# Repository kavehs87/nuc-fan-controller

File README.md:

# NUC fan control — one project, two halves

This repo is what `nuc-fan-controller` and the perfboard fan‑switch build became when they were merged in
October 2026. The fan‑switch history came across with it — 22 commits and the `checkpoint-fan-driver-v1`
and `checkpoint-pro-mini-v2` tags — parked under one directory, so nothing collided.

| half | what it holds | state |
|---|---|---|
| **`fan-switch-booster/`** | the gate booster that lets a 3.3 V logic pin switch a 12 V fan: its schematic, an ngspice model with hand‑written FET models, five sketches, the bench scripts | **built on perfboard, scoped, and listened to.** It is the electrical reference |
| **root** | the record of the NUC's own fan control: 4 577 paired 1 Hz samples in `bench/data/`, the analysers and graphs that read them, `BUILD.md`, and the sketches that carry the measured ITE constants | **measured.** The enclosure board that was designed around those numbers is retired to git at the tag `nuc-fan-controller-full-2026-10-23` |

**The perfboard is the reference.** Every claim about how a 12 V two‑pin fan behaves under a chopped
supply — carrier frequency, delivered duty, the fan's start threshold, what the noise actually was — comes
from that board and is recorded in `fan-switch-booster/README.md`. Every claim about how the NUC's ITE
behaves — its PWM frequency and amplitude, where its demand bottoms out, what it follows — comes from the
breadboard runs recorded below and in `BUILD.md`. The two were measured on the same machine, and they
complement each other; they do not agree on everything, and where they differ is written down rather than
smoothed over.

In October 2026 the repo was reduced to that: one KiCad project, the one that was simulated and
perfboard‑tested. The enclosure board's drawings, its exports, its board generator, the archived
tach‑simulator board and the two abandoned routings were removed, along with every KiCad cache and scratch
copy. They are complete at the tag named above, and no measurement went with them — the ITE runs were done
on a breadboard with an Uno.

## The tree

```
README.md                  this file — the merged record, and the measured facts both halves rest on
AGENTS.md                  what is settled, so it is not re-litigated
BUILD.md                   the NUC-side bench procedures: meter the header, the divider, the BC547 check,
                           the log pairs and offsets, calibration order  (its board sections are a
                           retired record; the commands in them no longer run)

bench/                     the ITE measurements
  data/                      12 raw 1 Hz logs — every number in this file comes from these
  analyze-*.py               the five analysers
  plot-curve.py plot-hold.py draw the two graphs in docs/bench/
  prepare-photos.py          the tool that cropped docs/bench/ from the phone originals; its input
                             directory was purged, so it no longer runs

docs/
  bench/                     five bench photographs, two graphs, and a README.md naming each one
  parts-collection.*         the parts sheet: §1 the perfboard build as it actually is, §2–3 the retired
                             board's cabinet walk, §4 the measurements that decide footprints

firmware/                  the sketches that made those measurements
  nuc-tach-modeB/            the ITE constants live here
  nuc-tach-modeA/            the archived tach simulator's sketch
  probe-*/                   the five breadboard probes

fan-switch-booster/        the built reference — its own README.md and AGENTS.md
  mosfet-fan-switch.kicad_sch   the schematic the perfboard was built from
  sim/                       ngspice model, hand-written FET models, ./sim/run.sh
  firmware/                  the sketch on the chip, three earlier variants, an Arduino-as-ISP programmer,
                             and the bench scripts (set.sh, seq.sh, flash-bootloader.sh, verify-flash.sh)
  pcb/  docs/pcb-*           the retired PCB record
  archive/                   the 5 V low-side first attempt
```

Three tags mark the states this repo has been through: `checkpoint-fan-driver-v1` and
`checkpoint-pro-mini-v2` from the fan‑switch work, and `nuc-fan-controller-full-2026-10-23`, which holds
everything the October 2026 cleanup removed.

## The facts both halves rest on

| fact | value | evidence |
|---|---|---|
| the machine | 6th‑generation i3 NUC, whose stock blower is a **5 V** fan | measured |
| the ITE's PWM request | **23 kHz** square, inside Intel's 25 kHz ±10 % | measured, scope |
| top of that swing | **≈ 4.90 V** on the wire, ≈ 2.45 V at a 10 k / 10 k tap | measured, extrapolated from the dwell ladder |
| the header's own fan supply | **5 V**, and a deliberate no‑connect on both boards | measured |
| the ITE's duty **floor** | **46–48 %** — 1 946 samples, none below 100 counts of 717. Under ITE control the fan never stops | measured |
| the duty is stepped | dwell rungs 198 / 257 / 320 / 380 counts, an 11.9‑point quantum | measured |
| what the demand follows | the **board / PCH temperature**, not the cores | measured, 4 577 paired samples |
| what a tach claim does to the demand | **1.1 %** for a 5.6× claim — reported speed is not in the loop | measured |
| tach read gain | 1 186 RPM against a 1 200 RPM claim, factor **0.990** | measured |
| tach ↔ RPM | `RPM = 30 × f_tach` (ITE IT8607E counts 2 pulses per turn) | measured |
| a 12 V two‑wire fan's start threshold | **4–7 V at its terminals**; 10 % and 20 % at 100 Hz deliver 1.2 V and 2.4 V and will not start it | measured on the perfboard |
| ATmega328P absolute maximum, any pin | **VCC + 0.5 V** = 3.8 V on a 3.3 V part | datasheet |
| Intel's published pinout for these headers | **there is none** — meter the four wires before splicing | `BUILD.md` |

The floor and the start threshold fit together, which is worth saying out loud: the ITE never asks for
less than ~47 %, and 47 % at 100 Hz is about 6.4 V at the fan terminals — above the voltage the fan needs
to start. So a fan driven by the ITE's demand is never asked to start from a dead stop, and the "start
kick" left open in `fan-switch-booster/README.md` only matters for manual control below about 30 %.

## Four ways the two designs disagree, and how to not mix them

The second column is retired hardware, but its sketch `firmware/nuc-tach-modeB` is still in this repo and
still carries the measured ITE constants — so these differences are live whenever a sketch crosses over.

| | the perfboard, `fan-switch-booster/` | the retired enclosure board |
|---|---|---|
| fan drive pin | **D9** (`OC1A`), Timer 1 | **D11** (`OC2A`), Timer 2 |
| tach pin | **D10**, and unused on the bench — that board has no tach path | **D9** (`OC1A`), sinking `Q1`'s open collector |
| polarity | non‑inverting: pin high → fan on | `Q2` inverts once — pin high → gate low → fan off — and `nuc-tach-modeB` asks for the complement to undo it |
| carrier | **100 Hz**, measured quiet | **31.25 kHz**, exactly 8 MHz / 256 |
| gate stage | `Q2` 2N7002 + `Q3` IRF7416 booster. Turn‑off costs a fixed **~170 µs**, because `/BOOT` charges back through `R3` 10 kΩ into a node that measures **~8 nF** | `Q2` BC547 with **`R8` 1 kΩ pulling the gate node to +12 V**, `R9` 120 Ω in series with `Q3`'s gate, `R10` 10 kΩ across gate‑to‑source. Turn‑off dumps through 120 Ω: τ ≈ 0.2 µs |
| ADC scale at the divider tap | **775 counts** — a 3.3 V reference | the logs are on an **Uno's 5 V** reference, where the same 2.50 V is **512 counts** |

**Both carriers are correct, for their own gate stage.** 31.25 kHz is safe on the BC547 board because its
gate dumps through 120 Ω in well under a microsecond; it is *unusable* on the perfboard, where the off
half‑period (16 µs) is far shorter than the 170 µs the booster needs to turn off, so the output is simply
stuck on. That is not a contradiction, it is two different circuits. Neither has to copy the other's carrier:
the ITE's 23 kHz is only *read* — the divider turns it into a DC level — and the fan drive frequency is a
free choice. Do not feed the ITE's clock into either output stage.

**And one thing that CAD never caught up with.** The bench settled on a **10 kΩ / 10 kΩ** divider — 2.50 V on
the tap, 0.8 V of headroom on a 3.3 V part — while the retired schematic still carried `R3` 4.7 k → `R4`
2.2 k in series from `NUC_PWM`, over `R5` 10 kΩ to ground: a **2.96 V** tap with 0.34 V of headroom. If that
board is ever rebuilt from the tag, it starts at two 10 kΩ, not at what the drawing says.

## Where the fan‑switch half lives

| in `fan-switch-booster/` | what it is |
|---|---|
| `README.md` | the whole record of that half: the stages, every part from the cabinets, the simulation, the perfboard findings, why the carrier is 100 Hz, the firmware and the flashing route |
| `AGENTS.md` | the settled list for that half — read it before touching that subtree |
| `mosfet-fan-switch.kicad_sch` | the schematic the perfboard was built from. **Live** |
| `mosfet-fan-switch.kicad_pcb`, `pcb/`, `docs/pcb-*` | **retired** board design — never built, never routed. Kept as the reason the layout looks like it does |
| `sim/` | the ngspice model. `./sim/run.sh` regenerates netlist, deck, plots and the variant tables |
| `firmware/fan-switch-freq/` | the sketch on the chip right now: boots itself at `duty 0 % OCR1A 0/10000 carrier 100 Hz` |
| `firmware/bench/` | `set.sh`, `seq.sh`, `flash-bootloader.sh`, `verify-flash.sh`, and how to run them on the remote bench |
| `archive/` | the 5 V low‑side first attempt — its schematic, its placeholder models and its plots |

---

# What the NUC does on its own — measured

Everything below this line is the record of the **ITE side**: how the NUC asks for fan speed, what its
demand follows, where it bottoms out, and how it reads a tach signal. It was measured on a breadboard with an
Uno standing in for the Pro Mini, and none of it depends on any board in this repo.

## The enclosure board that used to be here

`nuc-fan-controller` was a board meant to sit inside the NUC enclosure — last drawn as 88.90 × 76.20 mm on a
single copper layer, small enough to etch at home, after an earlier life as 124 × 85 mm on two. It did four
things: brought 19 V down to 12 V with an XL4016E1 module for three 12 V two‑pin fans; made 3.3 V for a Pro
Mini with an AMS1117‑3.3, with no 5 V rail anywhere on it; read the ITE's PWM request on A0 and re‑made it at
31.25 kHz on D11 through a BC547 stage into an IRFZ44N; and answered the tach with a Timer 1 square wave on
D9 sinking `Q1`'s open collector, the pull‑up living in the NUC. ERC clean, DRC clean, 0 unconnected items,
one deliberate no‑connect on its fan‑header connector's supply pin — the header's own fan supply, which it
never touched.

**It is retired, and it was never built.** The perfboard in `fan-switch-booster/` is the reference, so that
board's KiCad project, its `exports/` (schematic, board, the 1:1 copper etch prints, BOM, Gerbers), its board
generator in `logs/`, the archived tach‑simulator board and the two abandoned routings of the booster were
removed from the working tree in October 2026. All of it is intact in git at the tag
**`nuc-fan-controller-full-2026-10-23`** — every drawing, every export, and `10bc262`, the version that built
its 19 V → 12 V converter out of discrete parts instead of the module.

What stayed is measurement rather than board: `bench/data/` and the analysers that read it, the photographs
and graphs in `docs/bench/`, `BUILD.md`, `docs/parts-collection.md`, and the sketches that produced the
numbers.

## What is here for the NUC side

| File | What it is |
|---|---|
| `fan-switch-booster/` | **the built reference** — the perfboard booster, its schematic, its simulation, its sketches, its bench scripts. Table near the top of this file |
| `firmware/nuc-tach-modeB/nuc-tach-modeB.ino` | the sketch written for the retired board, and where the measured ITE constants live: `ITE_READ_GAIN`, the demand follower, the duty clamp |
| `firmware/probe-uno/probe-uno.ino` | breadboard probe sketch for an Uno (5 V / 16 MHz): tach wave on D9 with the measured `ITE_READ_GAIN` applied, 31.25 kHz fan drive on D11 — for scope-checking the BC547 stages before the board exists |
| `firmware/probe-gain/probe-gain.ino` | sweep sketch: an exact ladder of tach claims (900–3000 RPM, 20 s each) with the fan following the ITE's demand, printing the divider's own count — measures the ITE's read gain and logs its fan curve |
| `firmware/probe-loop/probe-loop.ino` | test sketch: fan drive pinned, tach claims stepped 800 / 2000 / 4500 RPM — measures whether the ITE's demand answers the tach at all |
| `firmware/probe-temp/probe-temp.ino` | test sketch: claim frozen at 1500 RPM — measures whether the demand answers temperature, and what the ITE's floor demand is when the machine is cold |
| `firmware/probe-divider/probe-divider.ino` | test sketch: measures the divider's own ratio with nothing but the Uno, by feeding the chain from the Uno's 5 V pin so the rail voltage cancels |
| `bench/analyze-ladder.py`, `bench/analyze-temp.py`, `bench/analyze-cold.py`, `bench/analyze-heat.py` | the analysers that produced the numbers below, run against `bench/data/` — `analyze-heat.py` is the one that separates the cores from the board |
| `bench/analyze-hold.py` | the analyser for the "does it integrate time?" test: flat-window trend, same-temperature early against late, and a two-variable fit |
| `bench/plot-curve.py`, `bench/plot-hold.py` | draw `docs/bench/06-ite-fan-response.svg` and `docs/bench/07-ite-hold-test.svg`, the two graphs below, from the same logs |
| `docs/bench/` | the five bench photographs and those two graphs, with `docs/bench/README.md` naming what each one shows |
| `bench/data/` | the raw logs: 1 Hz traces of the divider reading, and of the NUC's temperatures |
| `firmware/nuc-tach-modeA/nuc-tach-modeA.ino` | the archived tach simulator's sketch — the fixed‑RPM answer this project replaced |
| `bench/prepare-photos.py` | the tool that cropped `docs/bench/` out of the phone originals. Its input directory was purged in the cleanup, so it no longer runs; the recipe is in the file |
| `docs/parts-collection.md`, `.html` | the parts sheet, in two halves: **§1 the perfboard build as it actually is** — what is fitted, what is on the schematic but not on this bench, and what is on the shelf modelled but not fitted; §2–3 the **retired** board's cabinet walk, kept because those parts are still in the drawers and this is the record of where they came from; §4 the eight measurements that decide footprints, each one now marked *still live* or *retired board's footprint detail*. The `.html` is the same sheet with tick boxes |
| `BUILD.md` | the bench sheet: identifying the four header wires with a meter, setting a buck module to 12.0 V, the divider / top‑of‑swing procedure, the BC547 pin‑order check, calibration order. Its assembly steps name parts of the retired board |
| `fan-switch-booster/archive/` | the booster's first version — a single logic‑level IRLZ44N driven directly at 5 V, with its plots. Kept because the reason it worked is the reason 3.3 V needs a booster |

## On the bench

These measurements stand on their own. They were taken on a breadboard, with an Uno standing in for the Pro
Mini and the ITE's own behaviour logged at 1 Hz — no board in this repo was needed for any of them. Full
numbers and the raw logs are in `BUILD.md` and `bench/data/`; these are the readings that changed the design.

**The whole result in one picture** — 4 577 paired samples from five runs. Top: the ITE's requested duty
against the temperature of the *board* (`pch_thermal`), every sample as a dot, the heavy line being the
median in 3 °C bins, the dotted lines the dwell levels the ITE actually holds. The open circles are the
247 samples where the cores sat at 65 °C or hotter while the board stayed under 55 °C — they land on the
floor, not on the ramp, which is what makes the board the axis and the cores not. Bottom left: the fourth
run in time, board warmed by hand with the bench fans off and the NUC's own blower at minimum, then a
four‑core load, then left alone. Bottom right: the fifth run in time, held at 68.5–69 °C for sixteen flat
minutes — the duty sits on 378 counts for all of it. `bench/plot-curve.py` draws it from `bench/data/`.

**The harness into the NUC's fan header.** Four wires, no published pinout — `BUILD.md` identifies
them with a meter before anything is spliced. The tach and PWM wires go to the breadboard; the
header's own fan supply is left unconnected, which is the same pin the retired board marked as a deliberate
no‑connect.

**The duty‑read chain.** The ITE's PWM wire through the series resistors to the tap, the tap to A0,
the bottom resistor and the caps to ground. A0 sits at the tap — put it at the far end of the chain
and nothing divides, because the AVR draws no current.

**The ITE's PWM is 23 kHz, not an assumption.** A scope on the PWM wire reads a 23 kHz square at
45 % duty mid‑sweep — inside Intel's 25 kHz ±10 % for a 4‑wire fan. At that frequency the divider and
C10/C11 are comfortably over‑specified: τ = 4.49 ms against a 43.5 µs period leaves 7 mV of ripple at
the ADC, 0.24 % of the duty span.

**The tach is read, and it is read 1 % low.** The scope on the tach line:

and the NUC's own hardware monitor, 40.000 Hz later:

1186 against a 1200 claim, 1188 at the same setting a minute later — the ITE's display steps by
2 RPM, and the gap is 0.990. That is `ITE_READ_GAIN`. Note what is on the same screen: CPU 58 °C,
memory 44 °C, motherboard ambient 40 °C. Those are the ITE's own sensors, and they turn out to be
what its fan policy runs on.

**The demand answers the board's temperature, not the cores, and not the reported speed.** Five tests,
all logged at 1 Hz, 4 577 paired samples. Stepping the claimed RPM 800 → 2000 → 4500 — a 5.6× swing —
moved the ITE's requested duty by 1.1 %, while the same claim swung 195–260 counts on its own: the
reported speed is not in the loop. Freezing the claim at 1500 RPM and driving the package 55 → 83 → 53 °C
moved the reading 231 → 327 → 230 counts, correlated at **r = +0.822 with a 4 s lag** — but that run had
the bench fans switched by hand, so the board rose with the cores (PCH 52 → 63.5 °C) and the two could not
be told apart.

The third run tells them apart. Same sketch, same frozen claim, bench fans at maximum: `stress-ng --cpu 4`
for 300 s took the package 34 → 73 °C and it cooled back to 38 °C, the PCH only reached 55.5 °C, and
**the demand did not move at all** — 195–260 counts for eleven minutes, r = +0.049 against the cores. The
fourth run goes the other way and pushes the top end out: bench fans off, the NUC's own blower at minimum,
the board warmed by hand and then loaded, taking the board to 68.5 °C while the cores sat pinned at
88 °C. The demand climbed to **380 counts, 74 %**, with 434 counts (85 %) seen. Binned by the board, all
four runs together:

| board (`pch_thermal`) | n | median demand | as duty, 512 counts = 100 % | PWM wire average |
|---|---|---|---|---|
| 33–51 °C | 2 131 | 239 counts | 46.7 % | 2.33 V |
| 51–54 °C | 306 | 247 counts | 48.2 % | 2.41 V |
| 54–57 °C | 251 | 254 counts | 49.6 % | 2.48 V |
| 57–60 °C | 169 | 259 counts | 50.6 % | 2.53 V |
| 60–66 °C | 365 | 319 counts | 62.3 % | 3.12 V |
| 66–72 °C | 1 352 | 377 counts | 73.6 % | 3.68 V |

The decisive 247 samples have the cores at 68.7 °C and the board at 51.0 °C, and the ITE asks for exactly
what it asks for when everything is cold: 243 counts, 47 %, no sample above 261. `bench/analyze-heat.py`
reproduces these tables from the logs.

Two corrections to what this README said before the fourth run. The 297 counts it listed at 57–60 °C was
not a step the ITE holds — 285–314 counts account for 55 samples out of 4 577, while the four rungs
195–206, 253–264, 315–326 and 373–384 account for 667, 1 120, 321 and 826: the ITE dwells on rungs and
passes through everything else on its way between them.
And the demand does not chase the board at the same speed in both directions. In the fourth run the board
crossed 55 °C and the demand took **about 75 s** to reach its plateau, while on the way back it went
381 → 242 counts **within 30 s** of the board falling back through the same knee. The follower's 15 s tau
sits well inside both, so it filters the ITE's cycling without fighting its response.

**It is not an integrator: 20 minutes with the board held hot does not make the duty climb.** The theory
worth killing was that the ITE raises its duty for as long as the temperature refuses to fall — that it
integrates dwell time, and maybe accelerates past some threshold. The earlier runs could not touch it,
because in all of them the temperature was moving while the demand was being measured. The fifth run is
built for the question: a 300 s four‑core ramp to push the board past the knee, then **1200 s at a lighter
two‑core load** so the board sits still, then 300 s left alone. The board settled at 68.5–69 °C and stayed
there for sixteen flat minutes with the cores at 84–86 °C, and the demand sat at **378 counts** — the same
6/8 rung the fourth run found at the same board temperature, repeatable to 2 counts.

Three independent reads, all saying the same thing (`bench/analyze-hold.py`):

- Across the 16 windows where the board held within 0.8 °C of its plateau, the demand trended
  **+0.6 counts per minute** — and the board's own +0.07 °C/min drift already explains +1.5 counts per
  minute at the ladder's 20 counts per °C. Nothing is left over for time to explain.
- The same board temperature reached quickly against reached and held: at 63–66 °C, 342 counts on the ramp
  against **319** in the hold; at 66–69 °C, 378 against **368**. Later is *lower*, not higher.
- Fitting the 1 513 samples above the knee on board temperature **and** seconds since the knee was crossed:
  temperature alone gives R² 0.669, adding time gives 0.670 with a coefficient of **−0.00 counts per
  minute**. Time does not earn its place in the model.

What the run found instead is the opposite of a ratchet: held steady, **the ITE stops hunting**. Early in
the hold the reading swung 318–380 counts, dipping to the rung below; by the end the dips had shrunk to
346–381 and the mode was 379 throughout. And the ramp's overshoot — 342 counts at 63–66 °C on the way up
against 319 counts at the same temperature in the hold — says the ITE answers how *fast* the board is
moving as well as where it is, which is the same asymmetry the fourth run measured as 75 s to climb and
30 s to release. For the build this is a simplification: `DEMAND_TAU_S` does not have to outwait a
controller that ramps on a timer, because this one does not.

**The demand has a floor, and it is not near zero.** With the fans at maximum the package sat at 32–36 °C
for twelve minutes — 21 °C below the plateau the first temperature run had been stuck at — and the duty
did not follow it down: 196–260 counts, median 239, and not one sample of 717 below 100 counts. The floor
is 46–48 % duty, 2.33 V on the PWM wire, and it holds from the coldest measured board to a PCH of about
54 °C — 1 946 samples of it. So the fan this board drives never stops: `FAN_DUTY_MIN` is a clamp against a
broken sense wire rather than something the ITE ever reaches, and a fan that is always turning is a fan
whose tach claim is always plausible.

The fan also sits **inside** the ITE's loop — the fan cools the board, the ITE reads the board, the ITE
changes the demand — which is an enclosure requirement rather than a firmware one: air has to move across
the board and the ITE's own ambient sensor (the BIOS screen's "motherboard ambient", 40 °C against a CPU
at 58 °C), not only over the heatsink. The ITE will sit at its floor quite happily while the cores are at
73 °C.

**The demand is stepped, and the ladder holds across five runs.** The dwell levels are 198, 257, 320 and
380 counts, spaced 59–63, held for 667, 1 120, 321 and 826 samples of 4 577, and the hottest samples reach
434 — close to the fifth rung the spacing predicts, 441. A straight line through the four is counts = 15 + 61·k for k = 3, 4, 5, 6, so the step
is 11.9 duty points and 0.595 V on the wire: a binary duty quantum of 1/8, with the ITE sitting on 3/8 when
the board is cold and reaching 6/8 or 7/8 when it is hot. Read as 605 counts the step is 10.1 points and
matches nothing, which is one more reason the 10 kΩ / 10 kΩ divider is the right one. The cycling is fast —
535 of 716 seconds moved by more than 3 counts, one dwell switching to the other in 1–3 s — so the follower
filters it (tau 15 s, 1.5 duty point deadband) instead of pumping the fan at 0.3 Hz while the machine's own
thermal time constant is minutes. The cycle is the ITE closing its loop through the fan: it asks for more
duty, the board cools, it asks for less.

**The divider is settled: two 10 kΩ.** The tap is half the PWM line, so on the Uno 512 counts is 100 %
duty and every count in `bench/data/` reads on that scale. In volts, which is what a meter should agree
with: the ITE's four dwell levels — 198, 257, 320 and 380 counts — are **0.97 V, 1.26 V, 1.56 V and 1.86 V
at A0**, i.e. **1.94 V, 2.51 V, 3.13 V and 3.71 V average on the PWM wire**. That also argues for changing
the board's divider from 4.7 kΩ + 2.2 kΩ over 10 kΩ to 10 kΩ / 10 kΩ: 2.50 V on the tap instead of 2.96 V,
0.8 V of headroom on a 3.3 V part instead of 0.34 V, one fewer resistor, and bench and board reading the
same scale.

**One thing the bench still has to settle: the top of the PWM swing.** The four dwell levels now pin it
down without a scope. Extrapolated, the ladder reaches 15 counts (0.14 V) at zero duty and **502 counts
(4.90 V) at 8/8** — so the ITE's top is nearer 4.9 V than the 5.5 V the fan header's own supply would
suggest, and 100 % lands within 2 % of 512 counts rather than at 1009. Two things are still unexplained and
a meter settles both in one sitting: why the ladder has a 15‑count offset at zero (the ITE's output, or the
reading), and whether the top is flat or droops under load at the top dwell. The procedure is in `BUILD.md`.

## Bench order that carries over to any build

1. Identify the four NUC fan‑header wires with a meter — Intel publishes no pinout.
2. Set a buck module to 12.0 V with a meter before it is wired in and confirm its current limit is
   released; confirm 3.3 V at the regulator before it ever reaches a Pro Mini.
3. Find the fan's stall duty and measure its RPM at two duties. On the perfboard the stall is already
   bracketed: 20 % delivers ~2.4 V and will not start the fan, 30 % does.
4. Read the tach output with a frequency counter — it must equal `rpm / 30` Hz exactly, it is a hardware
   timer.
5. Wire the tach side first, then the PWM wire, then the fans.

**Three things that break hardware:** a 12 V fan's tach or PWM wire spliced into the NUC header
(that fan pulls those lines to its own 12 V internally), a 5 V FTDI on a 3.3 V Pro Mini
(ATmega328P absolute maximum on any pin is VCC + 0.5 V), and a BC547 fitted in the onsemi
**C‑B‑E** order when the footprint you are using is drawn for the NXP/Philips **E‑B‑C** order — meter
the two of them before they go in, `BUILD.md` says how. Flash with Board → *Arduino Pro or Pro
Mini*, Processor → **ATmega328 (3.3V, 8MHz)**.

## Reproducing the measurements

From the repo root, against the raw 1 Hz logs in `bench/data/`. Each Uno log is paired with its temperature
capture by a fixed offset in seconds — the Uno log has no timestamps — and these are the offsets the recorded
numbers were produced with:

```sh
# which temperature the ITE's demand follows: the table in *On the bench*
python3 bench/analyze-heat.py \
    bench/data/temp.log    bench/data/stress.log         -4 \
    bench/data/cold.log    bench/data/coldtemp.log        0 \
    bench/data/stress2.log bench/data/stress2-temps.log -15 \
    bench/data/warm.log    bench/data/warm-temps.log    -20 \
    bench/data/hold.log    bench/data/hold-temps.log    -20

# does the ITE integrate the time the board spends hot?
python3 bench/analyze-hold.py bench/data/hold.log bench/data/hold-temps.log -20

# the dwell rungs and the duty quantum
python3 bench/analyze-ladder.py bench/data/loop.log

# the two graphs
python3 bench/plot-curve.py
python3 bench/plot-hold.py bench/data/hold.log bench/data/hold-temps.log -20
```

Re‑run 2026‑10‑23, so this is verified rather than remembered: the five runs pair to 260 + 717 + 660 + 1 140
+ 1 800 = **4 577 samples**, `analyze-heat.py` reproduces the 2 131 / 306 / 251 / 169 / 365 / 1 352 board bins
and both discriminating subsets — 247 samples with the cores at 68.7 °C and the board at 51.0 °C at 243
counts, and 134 samples the other way round at 243 counts — and `analyze-ladder.py` reproduces the −1.1 %
answer to a 5.6× tach claim.

The plotters need matplotlib. The two shipped SVGs were drawn with **3.11.2**, which is not installed on this
machine; the venv that has matplotlib here has 3.10.3. Re‑running a plotter rewrites the tracked SVG with that
version's layout, so revert the change unless redrawing is what you wanted.

The booster's simulation, from `fan-switch-booster/`:

```sh
./sim/run.sh                                    # netlist -> ngspice -> variants -> plots
V=/Users/kaveh/Documents/Projects/schemdraw-mcp-server/.venv/bin/python3
$V sim/variants.py && $V sim/plot.py            # if the default python3 has no matplotlib
```

The board machinery that used to live in `logs/` — `build1l.py`, `layout.py`, `genwires.py`,
`applywires.py`, `verify.py`, `pourcheck.py`, `export.sh` — went with the retired board, and it was already
partly parked: `layout.py` and the wire generators still described the schematic as it was before it was
edited by hand, so running them would have undone work. All of it is at the tag.

One rule `genwires.py` enforced the hard way is worth keeping, because it is true of any KiCad sheet: **a
symbol pin or a name tag only connects to a wire *end***. A net whose wire carries a flag or a tag mid‑span
has to be written as the chain of segments it really is. Written as one straight wire, the flag and the tag
are orphaned and ERC reports them.

## Status

**Built, scoped and listened to:** the perfboard fan‑switch booster in `fan-switch-booster/`. Running at a
100 Hz carrier, quiet across the duty range, with the whole ladder heard.

**Measured and recorded:** the NUC's own fan control — its PWM frequency and amplitude, how it reads the
tach, what drives its demand, where that demand bottoms out and where it tops out, and that it does not
integrate the time the board spends hot. See *On the bench*; `BUILD.md` is the bench sequence.

**Retired:** the `nuc-fan-controller` enclosure board, and the archived boards before it. See *The enclosure
board that used to be here*.

**Open items:**

1. a sketch that reads `/DEMAND` on A0 and re‑makes it at the perfboard's own 100 Hz — the two halves
   joined, but the wire between them is not written yet;
2. the fan's exact start threshold, still only bracketed between 20 % and 30 % at 100 Hz, and the start kick
   that would make the bottom of the range usable;
3. `FAN_RPM_MIN`, `FAN_RPM_FULL` and `ADC_AT_100PCT` in `firmware/nuc-tach-modeB` are placeholders, and
   `ITE_READ_GAIN` was measured with an Uno — all four need the same measurement on a 3.3 V Pro Mini;
4. if the enclosure board is ever rebuilt, its divider starts at 10 kΩ / 10 kΩ, not the 4.7 k + 2.2 k over
   10 k the retired schematic still carries.

No license is granted — all rights reserved. It is published so the drawings and the reasoning
behind them are readable.

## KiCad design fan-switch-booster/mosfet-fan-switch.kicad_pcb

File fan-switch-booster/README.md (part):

# 12 V fan switched by 3.3 V logic — a gate booster built from my own parts

A KiCad schematic, a real ngspice simulation, and the same circuit **actually built and running on
perfboard** — of the thing every 3D printer needs: **an Arduino pin turning 12 V fans on and off
with a MOSFET.**  And since the design grew a NUC fan-header socket, the same Arduino can read the
NUC's own fan request and answer on its tachometer line.

**What is finished.** The perfboard build *is* the circuit: it runs, it is quiet across the duty
range, and it needs no replacement board. The KiCad board and `pcb/` are kept as the design record
— retired, not waiting to be routed or fabbed. The part of this project that actually changed
something is the measurement work under *Firmware, and why 0 % was humming*: why 0 % hummed, and why
the carrier is 100 Hz.

Every real component on this sheet is a part that actually sits in my parts cabinets
(`L1` and `R1`). Nothing here is a catalogue placeholder. The fan model is sized to the
fans I actually use: **100 mA each at 12 V.**

```
Arduino D9 (3.3 V PWM)
      |
     R1 1k ---- Q2  2N7002   level shifter: 3.3 V logic pulls /BOOT down to ~0 V
      |                |
     R2 10k          /BOOT ---- Q3  IRF7416 (P-ch)  gate booster: switches +12 V onto the gate
      |                |               |
     GND            R3 10k          R4 1k
                                     |
                                   /GATE ---- Q1  IRFZ44N  the switch that carries the fans
                                     |             |
                                    R5 10k       /DRAIN --- 12 V fan(s) --- +12 V
                                    GND             |
                                                 D1 1N5819 (flyback, cathode to +12 V)

NUC fan header J4
  PWM request 5 V --R7 10k--.  R8 10k to GND  -> /DEMAND 2.50 V at full request -> A0
  tach answer  <--Q4 BC547--  base via R9 1k from /TACH_PWM (D10, 100 Hz carrier)
  +12 V pin    not connected            the fans are powered by this board's own brick
```

Run everything with one command:

```bash
./sim/run.sh
```

It exports the netlist from the schematic, runs ngspice, writes five plots and two
comparison tables, and prints the numbers that matter. Output lands in `sim/out/`
(git-ignored).

---

## The stages, and the nets they live on

| net | what it is | who drives it |
|---|---|---|
| `/PWM` | the Arduino pin (D9 = OC1A, timer 1 channel A) | Arduino Pro Mini 3V3 |
| `/LGATE` | 2N7002 gate, held at 3.0 V by the R1/R2 divider | `/PWM` through R1 1k |
| `/BOOT` | booster node: +12 V when the pin is low, ~0 V when it is high | R3 10k up, Q2 down |
| `/HIGATE` | +12 V handed to the power FET by Q3 | Q3 IRF7416 |
| `/GATE` | IRFZ44N gate, settles at **10.91 V** | R4 1k from `/HIGATE`, pulled down by R5 10k |
| `/DRAIN` | the switching node under the fan(s) | Q1 IRFZ44N, clamped by D1 |
| `/FAN_W` | between a fan's winding and its drag resistance | fan model L1 + R6 |
| `/NUC_PWM` | the NUC's own fan request, 5 V at J4 pin 1 | the NUC (V3 in simulation) |
| `/DEMAND` | that request halved and smoothed for a 3.3 V ADC input | R7/R8 divider, C5 + C6 |
| `/TACH_PWM` | the Pro Mini's answer, D10 = OC1B, a 100 Hz carrier | Arduino Pro Mini 3V3 |
| `/TBASE` | `/TACH_PWM` after R9 1k, into Q4's base | R9 1k |
| `/NUC_TACH` | the tach line the NUC reads, pulled up inside the NUC | Q4 as an open collector |

**Why `/GATE` is 10.9 V and not 12 V.** A MOSFET gate draws no steady current, so R4 and
R5 are simply a divider: 12 V × 10 k / (1 k + 10 k) = 10.91 V. That is still deep inside the
region where the IRFZ44N's 17.5 mΩ is specified. R5 exists to keep the gate firmly at 0 V
when the pin is low, so the fan cannot drift on.

**Why the logic is not inverted.** Two inversions (Q2 inverts, Q3's P-channel orientation
inverts again) cancel. Pin high → fan on. At power-up the pin is floating, R2 keeps Q2 off,
so Q3 is off, so Q1 is off. The fans stay off.

**Why Q3's source must be the +12 V terminal.** A P-channel device's body diode conducts
drain → source. Wire Q3 the other way round and that diode feeds +12 V straight into
Q1's gate through R4 — the fans would be permanently on and no amount of code would fix it.
This is the single easiest way to get this circuit wrong, so the sheet draws Q3 rotated
180° with its source on the rail.

---

## The NUC fan-header link

The same board also talks to a PC. A NUC's 4-pin fan header wants to drive a fan itself:
it puts out a PWM **request**, expects a tachometer **answer** on the second pin, and
supplies the fan on the third. This board refuses both jobs and does them anyway:

```
NUC fan header J4                Pro Mini (on the board, U1)
  1  PWM request, 5 V ──R7 10k──┐
  2  tach answer   <──Q4 BC547──┼── D10 (OC1B)  /TACH_PWM  100 Hz carrier out
  3  fan supply    not connected│   (5 V on a 6th-gen NUC, 12 V on newer ones)
  4  GND ───────────────────────┴── GND (shared with the 12 V brick)
                                 A0  /DEMAND   2.50 V at full request, read as 775 counts
                                 D9  /PWM      the fan drive, unchanged
        R8 10k from /DEMAND to GND, with C5 1µ + C6 100n across it
```

- **The request has to be knocked from 5 V to 3.3 V** before it touches an Arduino pin.
  R7 (10 k, in series at the header) and R8 (10 k, to ground) halve it; C5 + C6 turn the
  23 kHz square wave into a DC level (τ = 5.49 ms, ≤ 5 mV ripple). Full request =
  **2.50 V = 775 counts**, 0.80 V of headroom. The NUC's PWM output only has to source
  **250 µA**.
- **The answer is an open collector**, because the pull-up lives in the NUC: R9 (1 k) into
  a BC547's base, collector on the tach line. 2.58 mA of base drive sinks 4.96 mA of
  pull-up current; the line lands at **0.037 V** low, 5.00 V high.
- **The tach carrier is a separate signal.** An ITE counts two pulses per revolution, so
  `RPM = 30 × f_tach`, and the legal window (700–10 500 RPM) is **23–350 Hz** on that
  wire. Copying the 1 kHz fan drive onto it would read 30 000 RPM and be rejected, so D10
  generates its own 100 Hz carrier (which reads 3 000 RPM). "Same PWM being sent to the
  fans" is the right *idea* — the frequency is what has to differ.
- J4 pin 3 (the NUC's own fan supply) is **not connected**: the fans are powered by this
  board's 12 V brick. Note that this supply is **not 12 V on every NUC** — a 6th-generation NUC
  drives its stock blower at **5 V**, and the ITE's PWM wire tops out near **4.9 V**, not the
  5.5 V a header supply would suggest. Nothing here depends on that pin, which is the point of
  leaving it unconnected.

### Measured on a real NUC — the record is at the root, not here

The ITE side of this design was assumed here and **measured** one directory up: 4 577 paired samples at
1 Hz on a 6th‑generation i3 NUC, logged in `../bench/data/`, analysed by `../bench/analyze-*.py`, and
tabulated with their evidence in **`../README.md`**, *The facts both halves rest on*. Read them there — they
are deliberately not repeated here. Those numbers govern, not the assumptions below.

Three of them decide how this board is used:

- the ITE's duty has a **46–48 % floor**, so under ITE control the fan never stops, and "the NUC controls
  the speed" means a ladder of roughly **47 % → 85 %**, not a knob. An actually stopped fan has to be a
  threshold in the sketch;
- a 5.6× tach claim moved the demand **1.1 %** — the tach answer exists to keep the BIOS happy, not to
  close a loop;
- the counts in `../bench/data/` are on an **Uno's 5 V** ADC reference, where 512 counts is full duty. On
  this board's **3.3 V / 8 MHz Pro Mini** the same 2.50 V tap is **775 counts**. Carry the calibration as
  volts, or multiply counts by 5 / 3.3.

The enclosure board those measurements were designed for — `nuc-fan-controller`, with its 19 V → 12 V
module, its BC547 gate stage and its 31.25 kHz drive on D11 — is **retired**: the perfboard here is the
reference. That design is intact in git at the tag `nuc-fan-controller-full-2026-10-23`, and the sketch
that carries the measured ITE constants, `../firmware/nuc-tach-modeB/nuc-tach-modeB.ino`, is still here.

`sim/nuc_link.py` (run by `./sim/run.sh`) is the check: duty-by-duty tap voltage, ripple,
ADC counts, the divider's load, the tach levels and the carrier window. Numbers and
caveats: `docs/pcb-notes.md`, *The NUC link*.

---

## Parts — all from my cabinets

| ref | part | package | cabinet · drawer | qty in bin |
|---|---|---|---|---|
| U1 | Arduino Pro Mini (3.3 V / 8 MHz, ATmega328P) | 35-hole module, on female sockets | L1 · C5 | 1 |
| Q1 | IRFZ44N N-channel power MOSFET | TO-220 | R1 · B4 | 12 |
| Q2 | 2N7002 N-channel MOSFET | SOT-23 | R1 · A4 | 11 |
| Q3 | IRF7416 P-channel MOSFET | SO-8 | R1 · A4 | 6 (+1 already on a breakout board) |
| Q4 | BC547 NPN small-signal transistor | TO-92 | R1 · D3 | 20 |
| D1 | 1N5819 Schottky, 40 V / 1 A | DO-41 | L1 · E1 | 30 |
| D2 | 1N5822 Schottky, 40 V / 3 A — **spare footprint, not soldered** | DO-27 | L1 · E1 | 9 |
| D3 | MBR10100CT Schottky, 100 V / 10 A dual — **spare footprint, not soldered** | TO-220 | L1 · E1 | 3 |
| R1, R4, R9 | 1 kΩ through-hole | axial | R1 · A2 | 20 |
| R2, R3, R5, R7, R8 | 10 kΩ through-hole | axial | R1 · B2 | 20 |
| C3, C6 | 100 n (104) ceramic disc | radial | L1 · C9 | 30 |
| C4 | 10 µ 16 V electrolytic | radial, 6.3 mm | L1 · C1 | 20 |
| C5 | 1 µ 50 V electrolytic | radial, 8 mm | L1 · E7 | 8 |
| V1 | Switching Power Supply Module, 12 V 450 mA | module | L1 · B7 | 2 |

These items on the sheet are **not** bin parts. They carry `dnp yes` (do not populate)
and have no footprint on the board:

- **C1 = 1.5 nF** — the IRFZ44N's own input capacitance (Ciss ≈ 1489 pF), drawn explicitly.
- **C2 = 1.7 nF** — the IRF7416's Ciss (≈ 1700 pF), drawn explicitly.
- **L1 = 10 mH + R6 = 120 Ω** — the fan. My bins hold no 12 V fan, so the fan is a model: an
  inductor for the winding and a resistor for the mechanical load. 12 V / 120 Ω = **100 mA**,
  which is what my real fans draw. Change R6 if yours are different: 80 Ω models a 150 mA fan.
- **V2, V3, V5** (VPULSE sources) stand in for the three pins: D9's fan drive, the NUC's
  5 V / 23 kHz request at J4 pin 1, and D10's 100 Hz tach carrier. **V4 + R10** stand in for
  the 5 V and 1 kΩ pull-up the NUC carries on its own tach line.
- The KiCad symbol for U1 is `mosfet-fan-switch:Arduino_Pro_Mini_328`, generated by
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
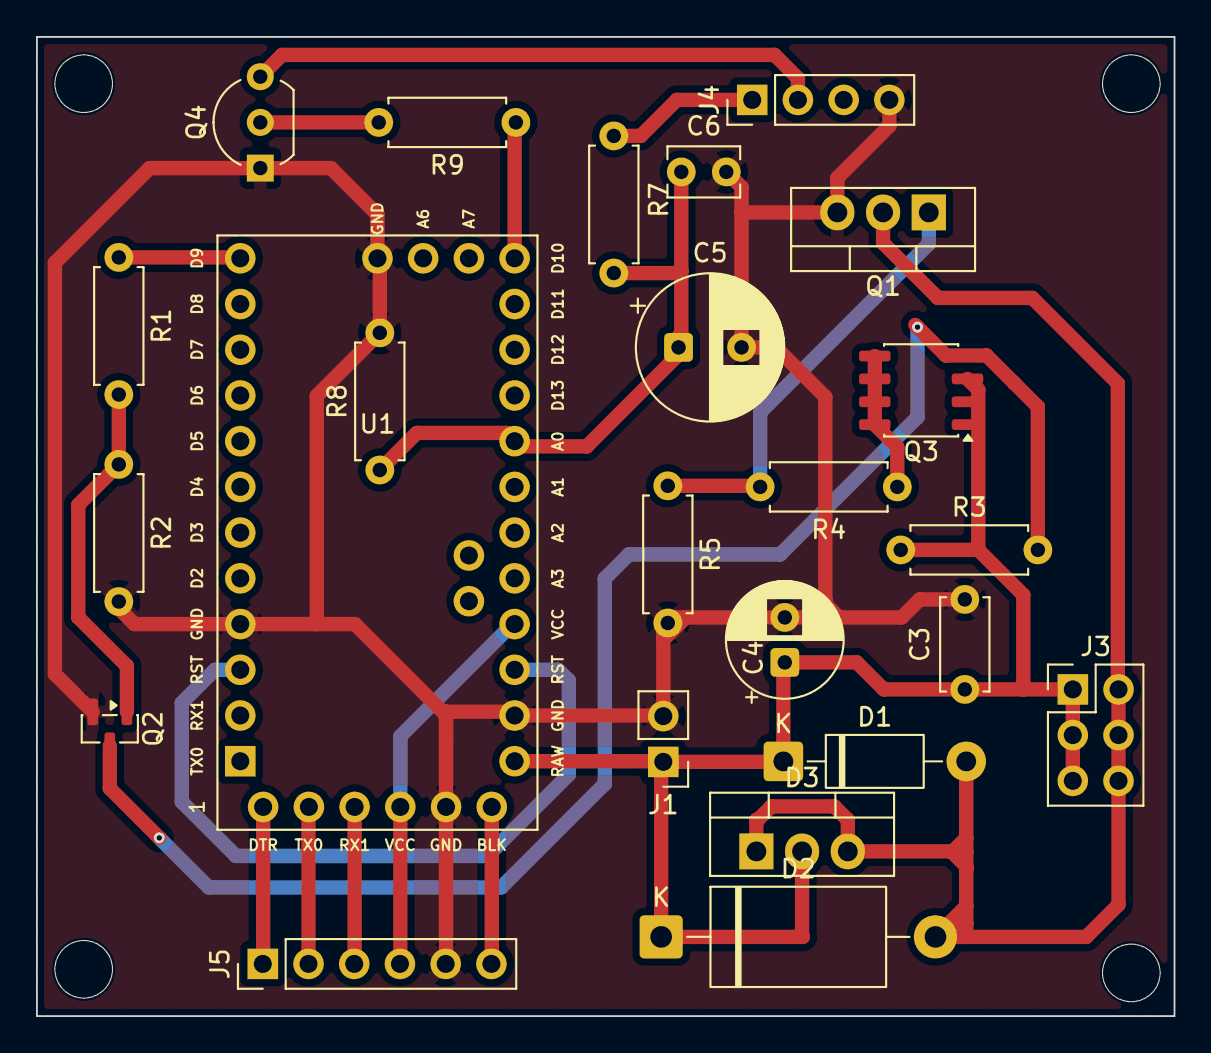
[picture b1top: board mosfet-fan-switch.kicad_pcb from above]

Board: 2 copper layers, 63.2 x 54.4 mm, 28 parts (0 on the bottom side), 19 nets.

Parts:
C3: 100n; C_Disc_D5.0mm_W2.5mm_P5.00mm
C4: 10u; CP_Radial_D6.3mm_P2.50mm
C5: 1u; CP_Radial_D8.0mm_P3.50mm
C6: 100n; C_Disc_D3.8mm_W2.6mm_P2.50mm
D1: 1n5819; D_DO-41_SOD81_P10.16mm_Horizontal
D2: 1n5822; D_DO-27_P15.24mm_Horizontal
D3: mbr10100ct; TO-220-3_Vertical
J1: 12V IN; PinHeader_1x02_P2.54mm_Vertical
J3: FAN OUT; PinHeader_2x03_P2.54mm_Vertical
J4: NUC FAN HEADER; PinHeader_1x04_P2.54mm_Vertical
J5: FTDI HEADER; PinHeader_1x06_P2.54mm_Vertical
MK1, MK2, MK3, MK4: M3 mounting hole; MountingHole_3.2mm_M3
Q1: irfz44n; TO-220-3_Vertical
Q2: 2n7002; SOT-23
Q3: irf7416; SO-8_3.9x4.9mm_P1.27mm
Q4: BC547; TO-92_Inline_Wide
R1, R4, R9: 1k; R_Axial_DIN0207_L6.3mm_D2.5mm_P7.62mm_Horizontal
R2, R3, R5, R7, R8: 10k; R_Axial_DIN0207_L6.3mm_D2.5mm_P7.62mm_Horizontal
U1: Arduino_Pro_Mini_3V3; Arduino_Pro_Mini_328_Socket

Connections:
/BLK: J5.6, U1.30 (BLK)
/BOOT: Q2.3 (D), Q3.4 (G), R3.2
/DEMAND: C5.1, C6.1, R7.2, R8.1, U1.20 (A0)
/DRAIN: D1.2 (A), D2.2 (A), D3.1 (A), D3.3 (A), J3.2, J3.4, J3.6, Q1.2 (D)
/DTR: J5.1, U1.25 (DTR)
/GATE: Q1.1 (G), R4.2, R5.1
/GND: C3.2, C4.2, C5.2, C6.2, J1.2, J4.4, J5.5, Q1.3 (S), Q2.2 (S), Q4.1 (E), R2.2, R5.2, R8.2, U1.4 (GND), U1.14 (GND), U1.29 (GND), U1.31 (GND)
/HIGATE: Q3.5 (D), Q3.6 (D), Q3.7 (D), Q3.8 (D), R4.1
/LGATE: Q2.1 (G), R1.2, R2.1
/NUC_PWM: J4.1, R7.1
/NUC_TACH: J4.2, Q4.3 (C)
/P3V3: J5.4, U1.16 (VCC), U1.28 (VCC)
/P12V: C3.1, C4.1, D1.1 (K), D2.1 (K), D3.2 (K), J1.1, J3.1, J3.3, J3.5, Q3.1 (S), Q3.2 (S), Q3.3 (S), R3.1, U1.13 (RAW)
/PWM: R1.1, U1.12 (D9)
/RST: U1.3 (RST), U1.15 (RST)
/RX1: J5.3, U1.27 (RX1)
/TACH_PWM: R9.1, U1.24 (D10)
/TBASE: Q4.2 (B), R9.2
/TX0: J5.2, U1.26 (TX0)

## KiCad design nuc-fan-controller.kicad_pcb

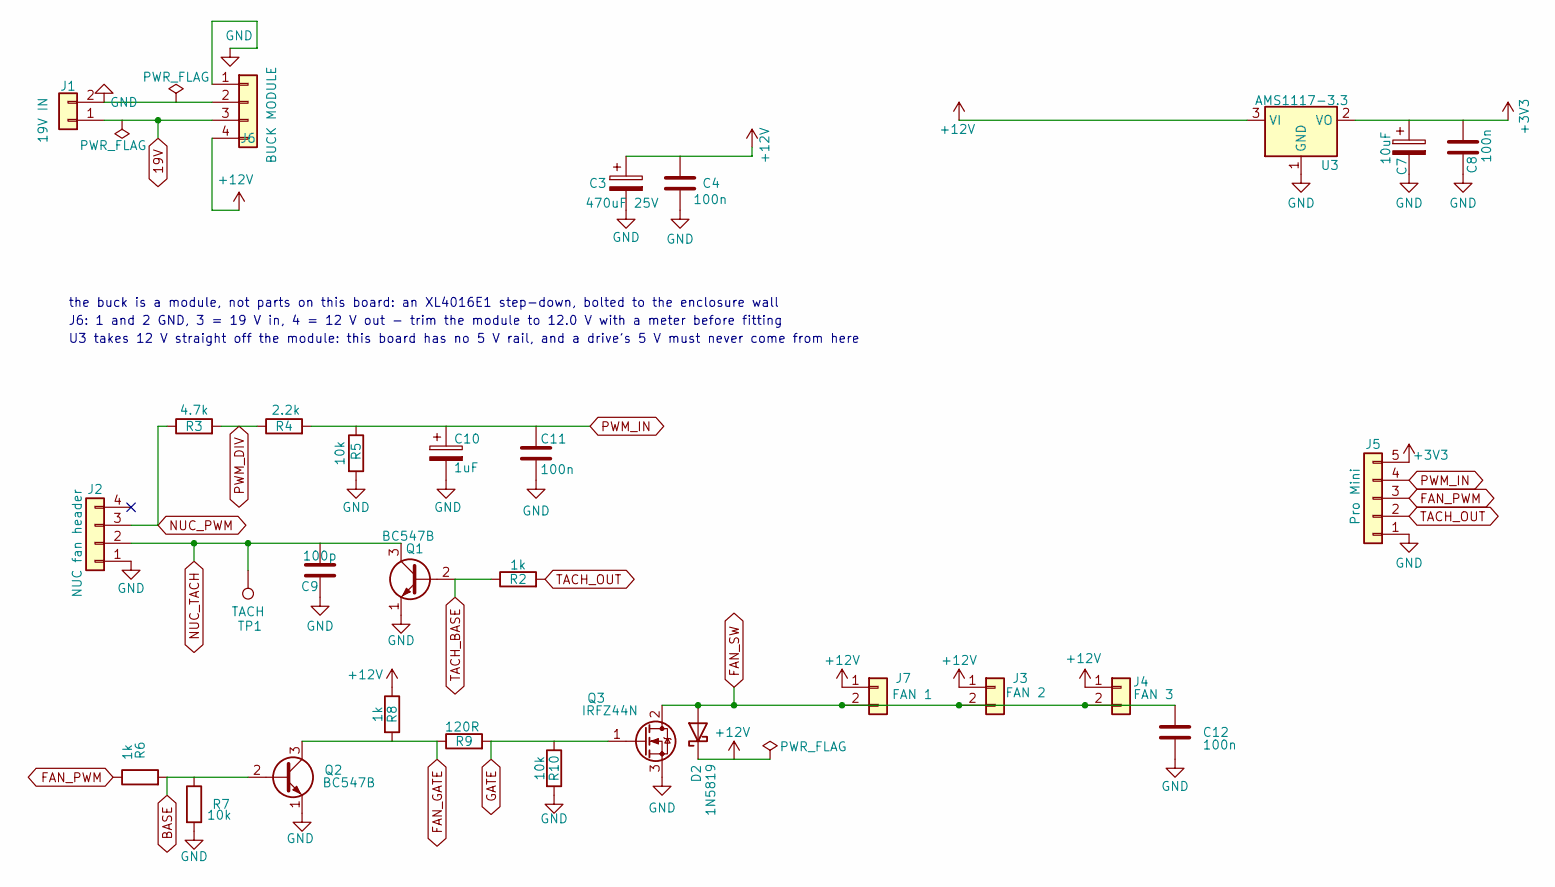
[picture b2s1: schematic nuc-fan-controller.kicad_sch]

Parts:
C3: 470uF 25V; CP_Radial_D8.0mm_P3.50mm
C4, C12: 100n; C_Disc_D6.0mm_W2.5mm_P5.00mm
C7: 10uF; CP_Radial_D6.3mm_P2.50mm
C8, C11: 100n; C_Disc_D3.8mm_W2.6mm_P2.50mm
C9: 100p; C_Disc_D3.8mm_W2.6mm_P2.50mm
C10: 1uF; CP_Radial_D6.3mm_P2.50mm
D2: 1N5819; D_DO-41_SOD81_P10.16mm_Horizontal
J1: 19V IN; PinHeader_1x02_P2.54mm_Vertical
J2: NUC fan header; FanPinHeader_1x04_P2.54mm_Vertical
J3: FAN 2; PinHeader_1x02_P2.54mm_Vertical
J4: FAN 3; PinHeader_1x02_P2.54mm_Vertical
J5: Pro Mini; PinHeader_1x05_P2.54mm_Vertical
J6: BUCK MODULE; PinHeader_1x04_P2.54mm_Vertical
J7: FAN 1; PinHeader_1x02_P2.54mm_Vertical
Q1, Q2: BC547B; TO-92_Inline_Wide
Q3: IRFZ44N; TO-220-3_Vertical
R2, R6, R8: 1k; R_Axial_DIN0204_L3.6mm_D1.6mm_P5.08mm_Horizontal
R3: 4.7k; R_Axial_DIN0204_L3.6mm_D1.6mm_P5.08mm_Horizontal
R4: 2.2k; R_Axial_DIN0204_L3.6mm_D1.6mm_P5.08mm_Horizontal
R5, R7, R10: 10k; R_Axial_DIN0204_L3.6mm_D1.6mm_P5.08mm_Horizontal
R9: 120R; R_Axial_DIN0204_L3.6mm_D1.6mm_P5.08mm_Horizontal
TP1: TACH; TestPoint_Pad_D1.5mm
U3: AMS1117-3.3; TO-252-3_TabPin2

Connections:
19V: J1.1, J6.3
+3V3: C7.1, C8.1, J5.5, U3.2 (VO)
+12V: C3.1, C4.1, D2.1 (K), J3.1, J4.1, J6.4, J7.1, R8.1, U3.3 (VI)
BASE: Q2.2 (B), R6.2, R7.1
FAN_GATE: Q2.3 (C), R8.2, R9.1
FAN_PWM: J5.3, R6.1; also elsewhere on the board
FAN_SW: C12.1, D2.2 (A), J3.2, J4.2, J7.2, Q3.2 (D)
GATE: Q3.1 (G), R9.2, R10.1
GND: C3.2, C4.2, C7.2, C8.2, C9.2, C10.2, C11.2, C12.2, J1.2, J2.1, J5.1, J6.1, J6.2, Q1.1 (E), Q2.1 (E), Q3.3 (S), R5.2, R7.2, R10.2, U3.1 (GND)
NUC_PWM: J2.3, R3.1
NUC_TACH: C9.1, J2.2, Q1.3 (C), TP1.1
PWM_DIV: R3.2, R4.1
PWM_IN: C10.1, C11.1, J5.4, R4.2, R5.1
TACH_BASE: Q1.2 (B), R2.1
TACH_OUT: J5.2, R2.2

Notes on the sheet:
the buck is a module, not parts on this board: an XL4016E1 step-down, bolted to the enclosure wall
J6: 1 and 2 GND, 3 = 19 V in, 4 = 12 V out - trim the module to 12.0 V with a meter before fitting
U3 takes 12 V straight off the module: this board has no 5 V rail, and a drive's 5 V must never come from here

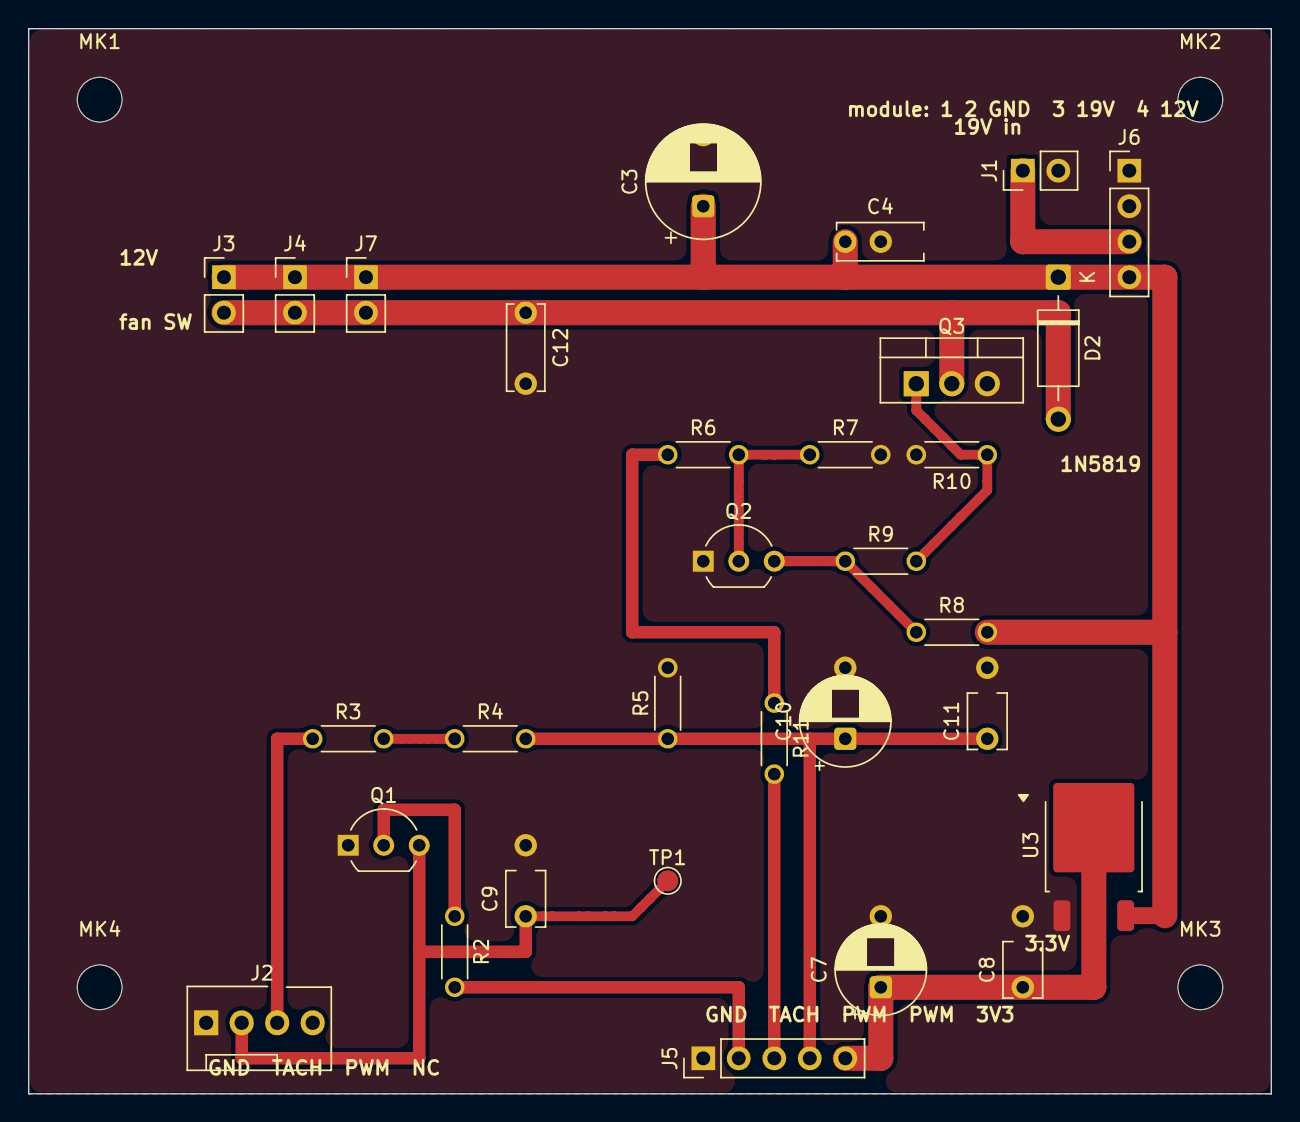
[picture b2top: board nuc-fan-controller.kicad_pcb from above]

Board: 2 copper layers, 88.9 x 76.2 mm, 35 parts (0 on the bottom side), 15 nets.

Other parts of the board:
MK1, MK2, MK3, MK4: M3; MountingHole_3.2mm_M3
R11: 0R bridge; R_Axial_DIN0204_L3.6mm_D1.6mm_P5.08mm_Horizontal

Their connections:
FAN_PWM: R11.1, R11.2; also elsewhere on the board

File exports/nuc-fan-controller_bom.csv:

"Refs","Value","Footprint","Qty","DNP"
"C3","470uF 25V","Capacitor_THT:CP_Radial_D8.0mm_P3.50mm","1",""
"C4","100n","Capacitor_THT:C_Disc_D6.0mm_W2.5mm_P5.00mm","1",""
"C7","10uF","Capacitor_THT:CP_Radial_D6.3mm_P2.50mm","1",""
"C8","100n","Capacitor_THT:C_Disc_D3.8mm_W2.6mm_P2.50mm","1",""
"C9","100p","Capacitor_THT:C_Disc_D3.8mm_W2.6mm_P2.50mm","1",""
"C10","1uF","Capacitor_THT:CP_Radial_D6.3mm_P2.50mm","1",""
"C11","100n","Capacitor_THT:C_Disc_D3.8mm_W2.6mm_P2.50mm","1",""
"C12","100n","Capacitor_THT:C_Disc_D6.0mm_W2.5mm_P5.00mm","1",""
"D2","1N5819","Diode_THT:D_DO-41_SOD81_P10.16mm_Horizontal","1",""
"J1","19V IN","Connector_PinHeader_2.54mm:PinHeader_1x02_P2.54mm_Vertical","1",""
"J2","NUC fan header","Connector:FanPinHeader_1x04_P2.54mm_Vertical","1",""
"J3","FAN 2","Connector_PinHeader_2.54mm:PinHeader_1x02_P2.54mm_Vertical","1",""
"J4","FAN 3","Connector_PinHeader_2.54mm:PinHeader_1x02_P2.54mm_Vertical","1",""
"J5","Pro Mini","Connector_PinHeader_2.54mm:PinHeader_1x05_P2.54mm_Vertical","1",""
"J6","BUCK MODULE","Connector_PinHeader_2.54mm:PinHeader_1x04_P2.54mm_Vertical","1",""
"J7","FAN 1","Connector_PinHeader_2.54mm:PinHeader_1x02_P2.54mm_Vertical","1",""
"Q1","BC547B","Package_TO_SOT_THT:TO-92_Inline_Wide","1",""
"Q2","BC547B","Package_TO_SOT_THT:TO-92_Inline_Wide","1",""
"Q3","IRFZ44N","Package_TO_SOT_THT:TO-220-3_Vertical","1",""
"R2","1k","Resistor_THT:R_Axial_DIN0204_L3.6mm_D1.6mm_P5.08mm_Horizontal","1",""
"R3","4.7k","Resistor_THT:R_Axial_DIN0204_L3.6mm_D1.6mm_P5.08mm_Horizontal","1",""
"R4","2.2k","Resistor_THT:R_Axial_DIN0204_L3.6mm_D1.6mm_P5.08mm_Horizontal","1",""
"R5","10k","Resistor_THT:R_Axial_DIN0204_L3.6mm_D1.6mm_P5.08mm_Horizontal","1",""
"R6","1k","Resistor_THT:R_Axial_DIN0204_L3.6mm_D1.6mm_P5.08mm_Horizontal","1",""
"R7","10k","Resistor_THT:R_Axial_DIN0204_L3.6mm_D1.6mm_P5.08mm_Horizontal","1",""
"R8","1k","Resistor_THT:R_Axial_DIN0204_L3.6mm_D1.6mm_P5.08mm_Horizontal","1",""
"R9","120R","Resistor_THT:R_Axial_DIN0204_L3.6mm_D1.6mm_P5.08mm_Horizontal","1",""
"R10","10k","Resistor_THT:R_Axial_DIN0204_L3.6mm_D1.6mm_P5.08mm_Horizontal","1",""
"TP1","TACH","TestPoint:TestPoint_Pad_D1.5mm","1",""
"U3","AMS1117-3.3","Package_TO_SOT_SMD:TO-252-3_TabPin2","1",""

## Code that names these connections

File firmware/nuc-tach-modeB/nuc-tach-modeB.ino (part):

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 * IRFZ44N is not a logic-level FET: its Vgs(th) is 2-4 V, so 3.3 V from a pin is not
 * enough to turn it on. Q2 (BC547B) is the level shifter - it is driven from the AVR,
 * and R8 1k pulls Q3's gate up to +12 V when Q2 is off. R7 10k holds Q2's base down
 * while the AVR's pins are inputs at reset, and R10 10k holds Q3's gate down if Q2's
 * collector ever floats.
 *
 * The gate loop, measured rather than waved at. With Q2 off the gate is fed from +12 V
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 * cost that matters is that the fan's real duty runs about 7 µs short of the commanded
 * one, which is why the RPM mapping is calibrated at the bench instead of derived here.
 *
 * Q2 inverts once: pin high -> Q2 on -> gate low -> Q3 off -> fan off. The sketch
 * inverts once more, so the fan finally sees the same duty the ITE asked for.
 *
 * D2 (1N5819) from FAN_SW to +12 V catches the fan's own inductive kick every time Q3
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// The ITE's tach gate is not exactly one second. Measured on a breadboard Uno into this NUC: a
// claim of 1200 RPM (40.000 Hz straight out of Timer1) read as 1188 in the BIOS - 0.9900 exactly.
// A scope says which side caused it: after applying a gain, if the tach line measures the gained
// frequency the ITE's gate is the reason and this constant belongs here; if it measures the
// ungained one, the driving board's oscillator is 1 % low and the number to fix is the one you
// measure on the finished board, not this one. Left at 1.0 until the Pro Mini is fitted.
const float ITE_READ_GAIN = 1.0f;      // emitted = wanted / gain; the Uno/NUC pair measured 0.9900
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const uint16_t ADC_AT_0PCT   = 0;
const uint16_t ADC_AT_100PCT = 918;

const uint8_t  PIN_TACH   = 9;    // OC1A -> R2 -> Q1 base
const uint8_t  PIN_FAN    = 11;   // OC2A -> R6 -> Q2 base
const uint8_t  PIN_PWM_IN = A0;   // R3/R4/R5 divider, C10/C11 filtered
const uint16_t UPDATE_MS  = 100;  // control period; also the serial report period
const float    RPM_SLEW   = 400.0f;  // RPM per update: 4000 RPM/s
const float    DEMAND_TAU_S    = 15.0f;  // the pole the ITE's demand is read through
const float    DEMAND_DEADBAND = 1.5f;   // duty points below which the fan is left alone

// -----------------------------------------------------------------------------
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
static float read_duty(void) {
  long sum = 0;
  for (uint8_t i = 0; i < 16; i++) sum += analogRead(PIN_PWM_IN);
  adc_seen = (uint16_t)(sum / 16);
  float adc = (float)adc_seen;
  float duty = (adc - (float)ADC_AT_0PCT) * 100.0f
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
  float duty = read_duty();

  // The demand is filtered hard, and the measurement is why. At a constant 33 C package this ITE
  // dwells at two duty levels 58 counts apart - 11 duty points - and ramps between them in 1-3 s:
  // 535 of 716 seconds moved by more than 3 counts. A 300 ms pole hands that whole dance to the fan,
  // which then pumps at about 0.3 Hz for no thermal reason. The signal worth following is +3.7 counts
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
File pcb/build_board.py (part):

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    #    collector that answers with the fan-drive carrier on the tach line.
    ("J4", "Connector_PinHeader_2.54mm:PinHeader_1x04_P2.54mm_Vertical",
     44.0, 49.0, 270, "F.Cu",
     {"1": "/NUC_PWM", "2": "/NUC_TACH", "4": "/GND"}),          # pin 3 = no connect
    ("R7", "Resistor_THT:R_Axial_DIN0207_L6.3mm_D2.5mm_P7.62mm_Horizontal",
     37.7, 49.0, 180, "F.Cu", {"1": "/NUC_PWM", "2": "/DEMAND"}),
    ("R8", "Resistor_THT:R_Axial_DIN0207_L6.3mm_D2.5mm_P7.62mm_Horizontal",
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    # J5 mirrors U1's own programming row pad for pad, so an FTDI/CH340 adapter
    # can plug in beside the module instead of on top of it.  Placed at 180
    # degrees so that J5 pin n sits straight across from U1 pin 24+n: pin 1
    # (DTR) at the bottom end of the board, pin 6 (BLK) at the band end.  One
    # column left of the GND descent, so MK4's courtyard stays clear of it.
    ("J5", "Connector_PinHeader_2.54mm:PinHeader_1x06_P2.54mm_Vertical",
     48.5, 85.73, 180, "F.Cu",
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
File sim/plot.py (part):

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
    fig, (ax1, ax2) = plt.subplots(1, 2, figsize=(11.6, 4.9))

    ax1.plot(vpin, vboot, lw=2.0, color="#d35400", label="/BOOT  (IRF7416 gate)")
    ax1.plot(vpin, vgate, lw=2.0, color="#2ca02c", label="/GATE  (IRFZ44N gate)")
    ax1.plot(vpin, vlgate, lw=1.2, color="#7d3c98", label="/LGATE (2N7002 gate)")
    ax1.set_xlabel("Arduino pin  V(PWM)  [V]")
    ax1.set_ylabel("voltage  [V]")
    ax1.set_ylim(-1, 13)
    ax1.grid(True, alpha=0.3)
    ax1.legend(fontsize=8, loc="center right")
    ax1.set_title("the booster: 3.3 V in, a 10.9 V gate out")
    ax1.annotate("pin low: 2N7002 off,\n/BOOT sits at 12 V through R3,\nIRF7416 off, /GATE at 0 V",
                 (0.15, 11.4), fontsize=8, color="0.35")
    ax1.annotate("pin high: 2N7002 on,\n/BOOT ~ 0 V, IRF7416 on,\n/GATE = 12 V x R5/(R4+R5) = 10.9 V",
                 (1.6, 8.6), fontsize=8, color="0.35")

    ax2.plot(vpin, vdrain, lw=2.0, color="#c0392b", label="V(drain)")
    ax2.set_xlabel("Arduino pin  V(PWM)  [V]")
    ax2.set_ylabel("V(drain)  [V]", color="#c0392b")
    ax2.set_ylim(-0.5, 13)
    ax2.grid(True, alpha=0.3)
    ax2b = ax2.twinx()
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
    fig, axes = plt.subplots(4, 1, figsize=(10, 10.6), sharex=True)
    axes[0].plot(t_ms, vpwm, lw=1.0, color="0.55", label="Arduino D9 (PWM)")
    axes[0].plot(t_ms, vboot_t, lw=1.6, color="#d35400", label="/BOOT (P-FET gate)")
    axes[0].plot(t_ms, vgate_t, lw=1.8, color="#2ca02c", label="/GATE (power FET gate)")
    axes[0].set_ylabel("voltage [V]")
    axes[0].set_title("3.3 V PWM -> 2N7002 -> IRF7416 -> IRFZ44N -> 12 V fan   (1 kHz, 50 %)")
    axes[0].legend(loc="upper right", fontsize=8)

    axes[1].plot(t_ms, vdrain_t, lw=1.2, color="#c0392b")
    axes[1].set_ylabel("V(drain) [V]")
    axes[1].set_ylim(-0.5, 14)
    axes[1].grid(True, alpha=0.3)
    axes[1].annotate("12.36 V: the fan's inductance flies the node up,\nthe 1N5819 clamps it at 12 V + Vf",
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    fig, axes = plt.subplots(1, 2, figsize=(11.6, 4.8))
    axes[0].plot(t[m_on] * 1e6, vpwm[m_on], lw=1.2, color="0.55", label="Arduino pin")
    axes[0].plot(t[m_on] * 1e6, vboot_t[m_on], lw=1.8, color="#d35400", label="/BOOT")
    axes[0].plot(t[m_on] * 1e6, vgate_t[m_on], lw=2.0, color="#2ca02c", label="/GATE")
    axes[0].set_xlabel("time after the pin goes high  [µs]")
    axes[0].set_ylabel("voltage [V]")
    axes[0].set_ylim(-1, 13)
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                     (4.0, 3.0), fontsize=8, color="#2ca02c")
    axes[0].legend(fontsize=8, loc="center right")

    axes[1].plot(t[m_off] * 1e6, vdrain_t[m_off], lw=2.0, color="#c0392b", label="V(drain)")
    axes[1].axhline(12.37, ls="--", lw=1.0, color="0.4")
    axes[1].annotate("clamped at 12 V + 0.36 V by the 1N5819", (555, 11.0), fontsize=8, color="0.3")
    axes[1].annotate("/BOOT must charge back to 12 V through R3:\ntau = 10 kohm x 1.7 nF = 17 us\n-> /GATE takes tens of us to fall",
                     (545, 3.5), fontsize=8, color="#d35400")
    axes[1].set_xlabel("time around the pin going low  [µs]")
    axes[1].set_ylabel("V(drain) [V]", color="#c0392b")
    axes[1].set_ylim(-1, 14)
    axes[1].set_title("turn-off: the fan's inductance flies the node up")
    axes[1].grid(True, alpha=0.3)
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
